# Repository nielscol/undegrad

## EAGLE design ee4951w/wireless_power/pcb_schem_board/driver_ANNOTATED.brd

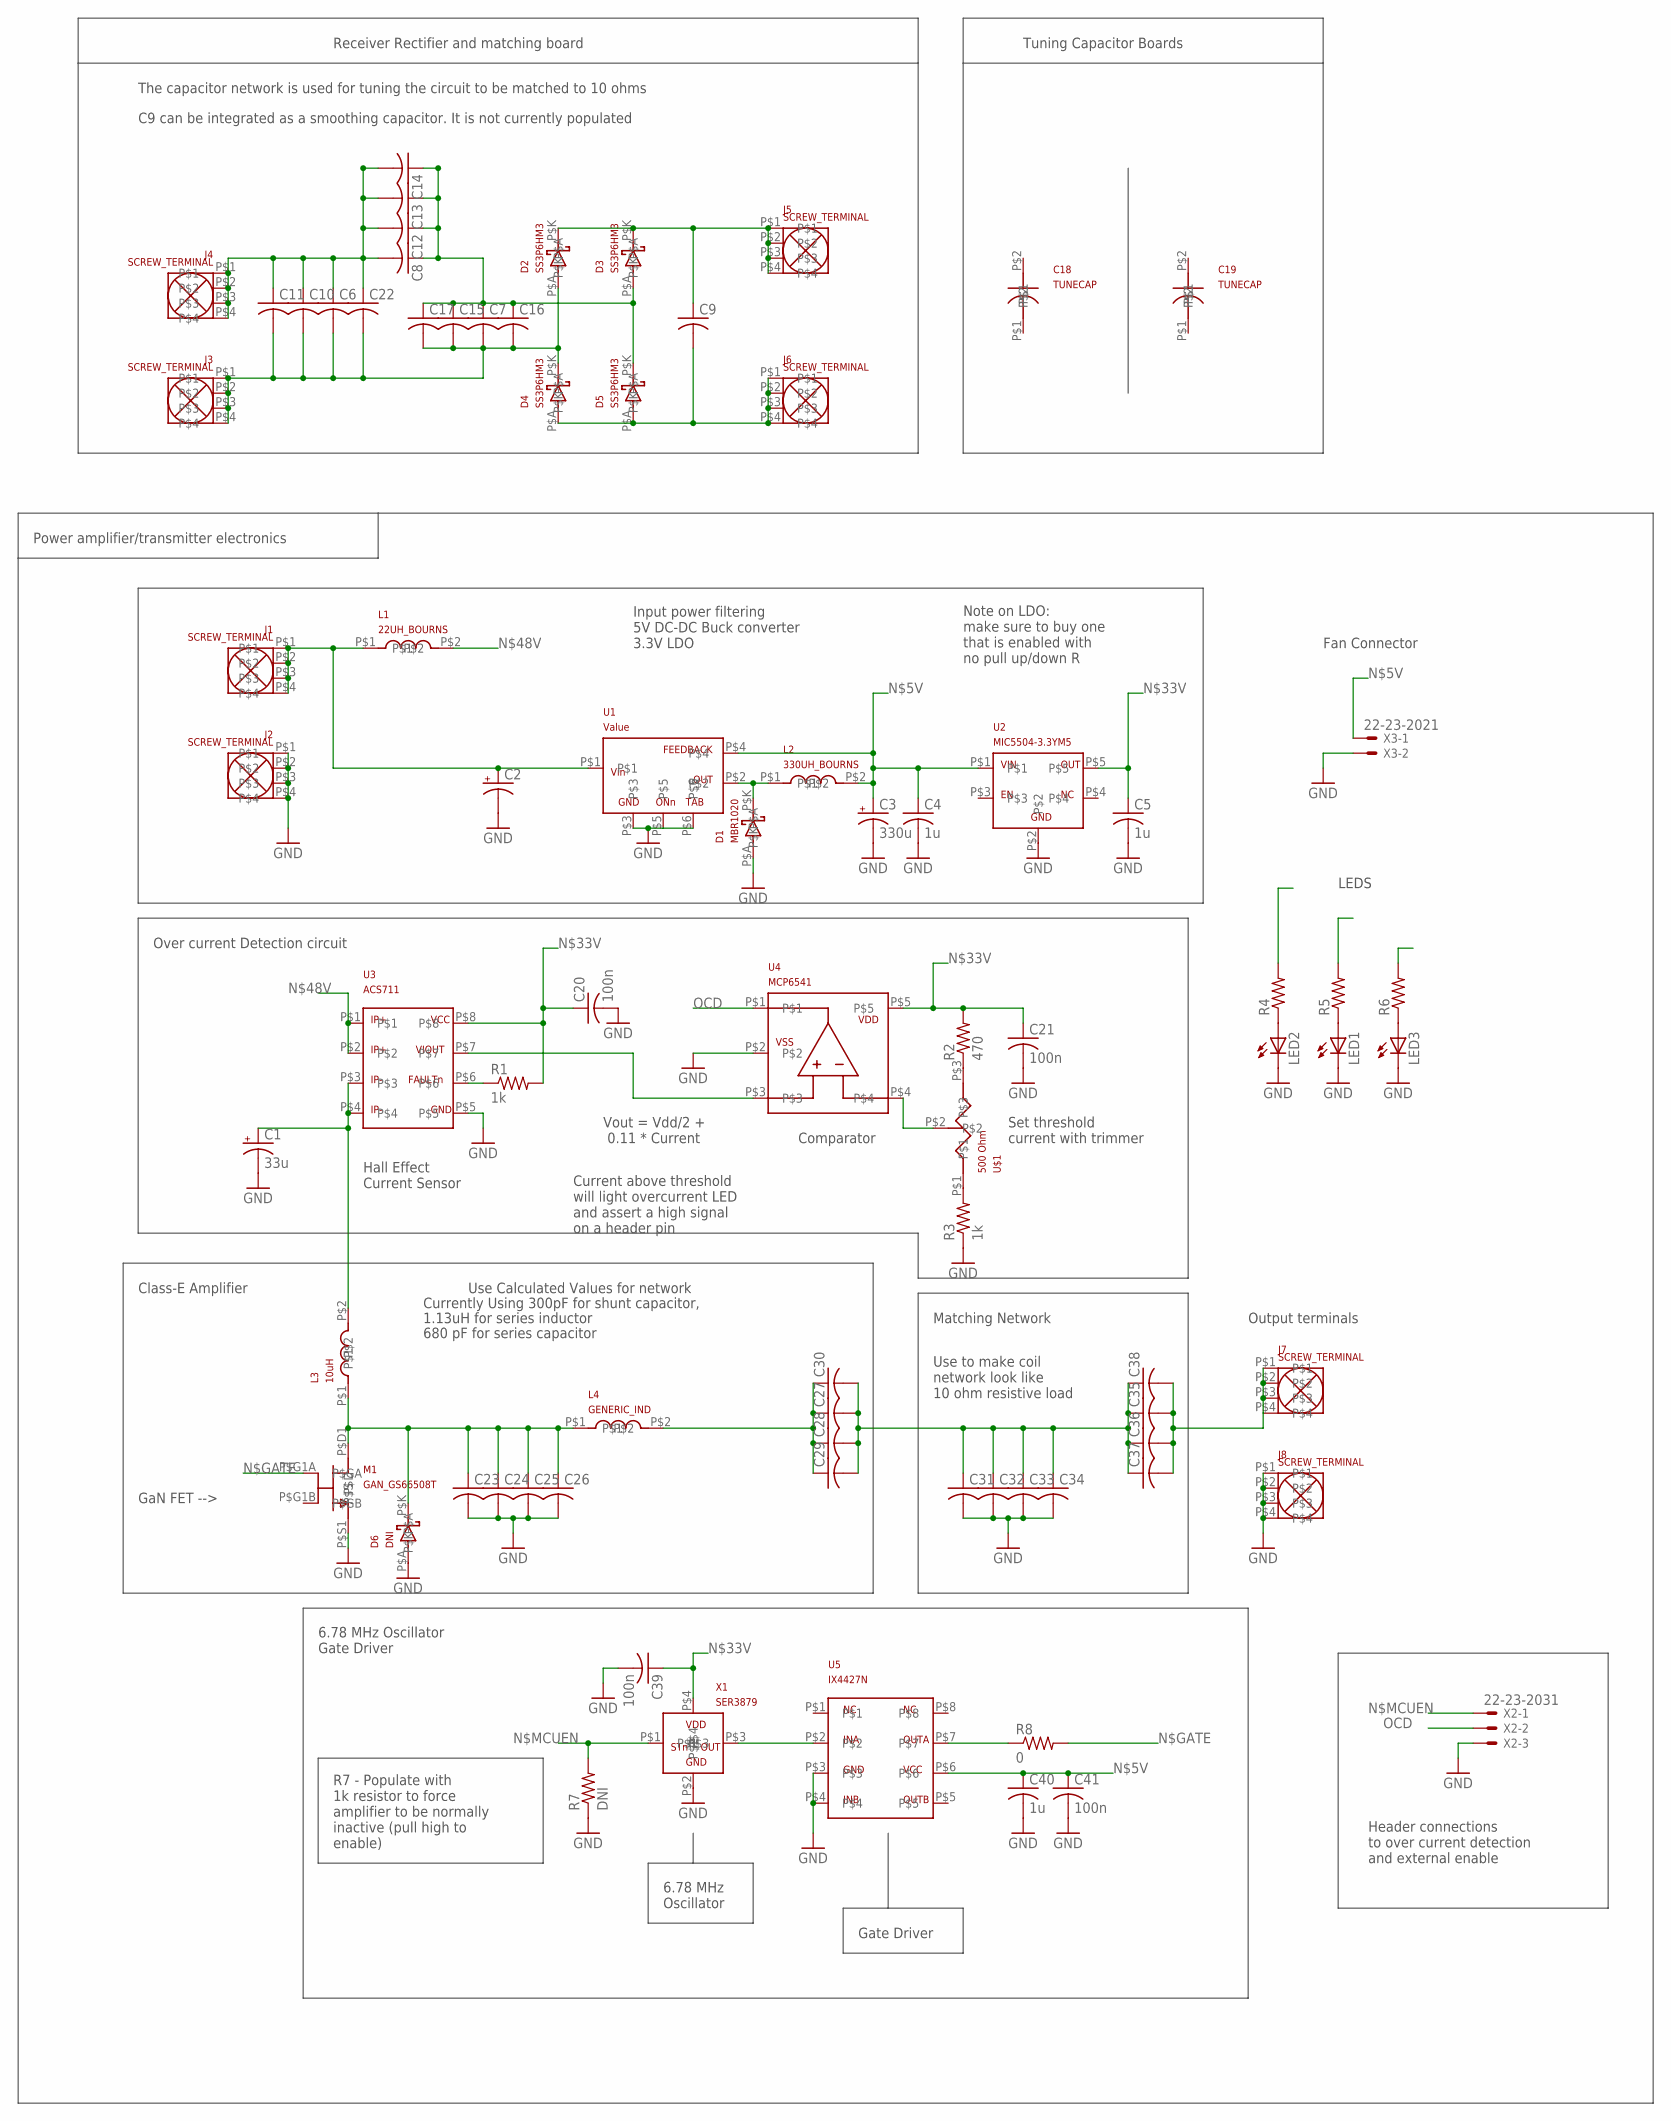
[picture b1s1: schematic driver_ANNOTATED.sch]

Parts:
C1: 33u; 140CLH-0810
C2: CPOL-US140CLH-1010; 140CLH-1010
C3: 330u; 150CLZ-0810
C4, C5, C40: 1u; C0603K
C6, C7, C8, C9, C10, C11, C12, C13, C14, C15, C16, C17, C22, C23, C24, C25, C26, C27, C28, C29, C30, C31, C32, C33, C34, C35, C36, C37, C38: C-USC1206K; C1206K
C18, C19: TUNECAP; CAPTUNE
C20: 100n; C0603
C21, C39, C41: 100n; C0603K
D1: MBR1020; SOD-123
D2, D3, D4, D5: SS3P6HM3; D0-220
D6: DNI; D0-220
J1, J2, J3, J4, J5, J6, J7, J8: SCREW_TERMINAL
L1: 22UH_BOURNS; 492MIL_IND
L2: 330UH_BOURNS; 330U_IND
L3: 10uH; GENERIC_IND
L4: GENERIC_IND
LED1, LED2, LED3: LEDCHIPLED_0805; CHIPLED_0805
M1: GAN_GS66508T
R1, R3: 1k; R0603
R2: 470; R0603
R4, R5, R6: R-US_R0603; R0603
R7: DNI; R0603
R8: 0; R0603
U1: TL2575HV
U2: MIC5504-3.3YM5
U3: ACS711; IX4427N
U4: MCP6541; SC-70-5
U5: IX4427N
U$1: 500 Ohm; TRIMMER
X1: SER3879; SER3879-ND
X2: 22-23-2031
X3: 22-23-2021

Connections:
GND: C1.-, C2.-, C3.-, C4.2, C5.2, C20.2, C21.2, C23.2, C24.2, C25.2, C26.2, C31.2, C32.2, C33.2, C34.2, C39.2, C40.2, C41.2, D1.P$A, D6.P$A, J2.P$1, J2.P$2, J2.P$3, J2.P$4, J8.P$1, J8.P$2, J8.P$3, J8.P$4, LED1.C, LED2.C, LED3.C, M1.P$S1 (P$S), R3.1, R7.1, U1.P$3, U1.P$5, U1.P$6, U2.P$2, U3.P$5, U4.P$2, U5.P$3, U5.P$4, X1.P$2, X2.3, X3.2
unnamed: D1.P$K, L2.P$1, U1.P$2
unnamed: C2.+, J1.P$1, J1.P$2, J1.P$3, J1.P$4, L1.P$1, U1.P$1
unnamed: C6.2, C7.2, C10.2, C11.2, C15.2, C16.2, C17.2, C22.2, D2.P$A, D4.P$K, J3.P$1, J3.P$2, J3.P$3, J3.P$4
unnamed: C6.1, C8.2, C10.1, C11.1, C12.2, C13.2, C14.2, C22.1, J4.P$1, J4.P$2, J4.P$3, J4.P$4
unnamed: C7.1, C8.1, C12.1, C13.1, C14.1, C15.1, C16.1, C17.1, D3.P$A, D5.P$K
unnamed: C3.+, C4.1, C40.1, C41.1, L2.P$2, R4.2, U1.P$4, U2.P$1, U5.P$6, X3.1
unnamed: C9.2, D4.P$A, D5.P$A, J6.P$1, J6.P$2, J6.P$3, J6.P$4
unnamed: C9.1, D2.P$K, D3.P$K, J5.P$1, J5.P$2, J5.P$3, J5.P$4
unnamed: C1.+, L3.P$2, U3.P$3, U3.P$4
unnamed: U3.P$7, U4.P$3
unnamed: R1.1, U3.P$6
unnamed: R2.1, U$1.P$3
unnamed: R3.2, U$1.P$1
unnamed: U4.P$4, U$1.P$2
unnamed: C23.1, C24.1, C25.1, C26.1, D6.P$K, L3.P$1, L4.P$1, M1.P$D1 (P$D)
unnamed: C27.1, C28.1, C29.1, C30.1, L4.P$2
unnamed: LED2.A, R4.1
unnamed: LED1.A, R5.1
unnamed: LED3.A, R6.1
unnamed: C27.2, C28.2, C29.2, C30.2, C31.1, C32.1, C33.1, C34.1, C35.1, C36.1, C37.1, C38.1
unnamed: R8.1, U5.P$7
unnamed: U5.P$2, X1.P$3
unnamed: C5.1, C20.1, C21.1, C39.1, R1.2, R2.2, U2.P$5, U3.P$8, U4.P$5, X1.P$4
unnamed: C35.2, C36.2, C37.2, C38.2, J7.P$1, J7.P$2, J7.P$3, J7.P$4
unnamed: L1.P$2, U3.P$1, U3.P$2
N$GATE: M1.P$G1A (P$GA), R8.2
N$MCUEN: R6.2, R7.2, X1.P$1, X2.1
OCD: R5.2, U4.P$1, X2.2

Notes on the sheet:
Power amplifier/transmitter electronics
Receiver Rectifier and matching board
C9 can be integrated as a smoothing capacitor. It is not currently populated
The capacitor network is used for tuning the circuit to be matched to 10 ohms
Tuning Capacitor Boards
GaN FET -->
6.78 MHz Oscillator Gate Driver
R7 - Populate with 1k resistor to force amplifier to be normally inactive (pull high to enable)
6.78 MHz Oscillator
Gate Driver
Header connections to over current detection and external enable
Class-E Amplifier
Use Calculated Values for network
Currently Using 300pF for shunt capacitor,
1.13uH for series inductor
680 pF for series capacitor
Use to make coil network look like 10 ohm resistive load
Output terminals
Over current Detection circuit
Hall Effect Current Sensor
Comparator
Vout = Vdd/2 + 0.11 * Current
Set threshold current with trimmer
Current above threshold will light overcurrent LED and assert a high signal on a header pin
Input power filtering 5V DC-DC Buck converter 3.3V LDO
Note on LDO: make sure to buy one that is enabled with no pull up/down R
Fan Connector
LEDS
Matching Network

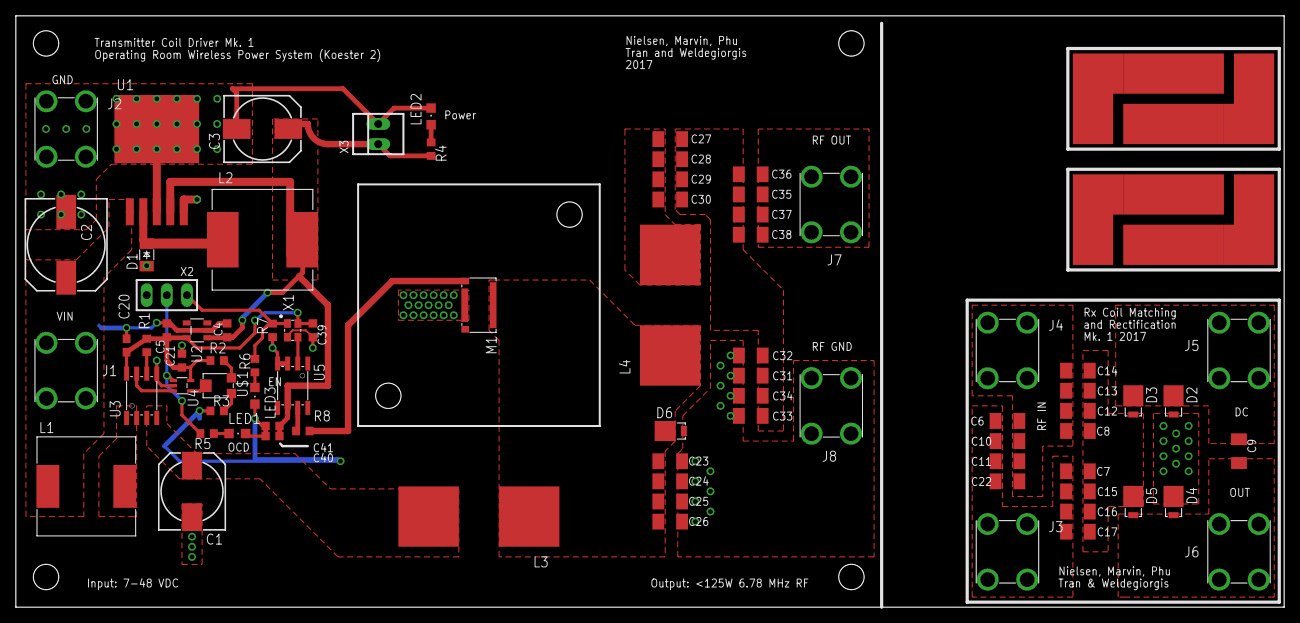
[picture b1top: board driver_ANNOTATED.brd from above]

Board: 2 copper layers, 160.0 x 74.6 mm, 80 parts (0 on the bottom side), 29 nets.

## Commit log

2020-07-07 Bulk of files from undergrad
